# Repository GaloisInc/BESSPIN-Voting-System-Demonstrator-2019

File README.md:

# The BESSPIN Voting System

## Galois and Free & Fair, May-September 2019

# Overview

Galois and Free & Fair are pleased to present the BESSPIN Voting
System (BVS).

The BESSPIN Voting System (BVS) is a demonstration system being funded
by DARPA’s SSITH (System Security Integrated Through Hardware and
Firmware) program. SSITH’s goal is to develop new technologies that
will enable chip designers to safeguard hardware against all known
classes of software-exploitable vulnerabilities, such as memory
errors, information leakage, and code injection.

The BVS demonstration system is intended to showcase the SSITH
program’s results by showing how the innovations of “securitized
hardware” could be applied to a type of critical computing system that
is personally familiar both in use and in importance to millions of
Americans: voting systems. BVS is a combination of voting-system
demonstration software together with prototypes of securitized
hardware being developed by SSITH researchers.

This public repository provides prospective adversarial testers with
complete information, tools, specifications, and source code that was
used to develop the 2019 release of the BVS. The intent is to provide
the most open possible approach to testing, enabling testers to obtain
the full build environment for the BVS, to build it from original
sources, assess its strengths and weaknessess, and plan and develop
possible exploits to compromise the BVS.  

However, not every tester will wish to start with this “Build First”
approach. Others may wish to begin with the “Attacker Quickstart”
information in order to learn and use the tools and reference exploits
provided for testers. Still others may wish to learn about the BVS
with a more manageable “short list” of documentation and information,
rather than exploring the full repository.

# For All Testers

All testers should begin by reading the [Overview of BESSPIN Voting
System](Overview-of-BESSPIN-Voting-System.pdf) document at the top
level of this repository. This document provides essential information
about the current BVS release, the 2019 goals, and limits on testing
including the threat model and win conditions.

# Attacker Quickstart

The top-level directory [Attacker-Quickstart](Attacker-Quickstart)
provides the next level of information after the [Overview of BESSPIN
Voting System](Overview-of-BESSPIN-Voting-System.pdf) document
document, specifically about the facilities provided for exploit
development.

# Documentation on BVS

The top-level directory [BVS-Documents](BVS-Documents) provides the
next level of information after the [Overview of BESSPIN Voting
System](Overview-of-BESSPIN-Voting-System.pdf) document, about the BVS
system’s design and functions.

System design documentation is found in the [docs directory](docs).
In particular, that directory contains:
 - the [BVS 2020 System Specification](docs/BVS 2020 system specification.md)
 - the [BVS 2020 Protocol Specification](docs/protocol.md)
 - the [Smart Ballot Box Specification](docs/sbb.md)
  
# Support for System Build

The remainder of this repository provides the ability to build the BVS
including source code [source](source); specifications [specs](specs);
hardware sketches and schematics [hardware](hardware); documentation
of the build environment [developer-documents](developer-documents);
the top-level [`Makefile`](Makefile) and related files
(`burn_to_flash.sh`, `startup.gdb`); and `.git*` files.

In addition, there is one other source directory for a component that
is not part of the BVS per se, but is part of the test
environment. The [http-log-listener](http-log-listener) directory has
the source code for a software component that runs on a separate
dedicated server that shares the test environment’s LAN with the BVS
Smart Ballot Box systems. The logging software’s purpose is to receive
log data sent by each Smart Ballot Box. Such log consolidation is an
important convenience for the operators of the test environment to be
able to view the activity occuring on the Smart Ballot Box units as
the testers interact with them.

This repository also contains submodules for dependencies that we
manage in other git repositories:
- the RISC-V port of FreeRTOS, which is the lightweight real-time OS
  used for the BVS Smart Ballot Box;
- the top-level toolset for the BESSPIN project;
- the “government furnished equipment” (GFE) repository, which
  contains bitstreams to be uploaded on the FPGAs, and nix shell
  scripts for build set-up.

In order to update those submodules, remember to either clone the
repository using the `--recursive` switch or use the `git submodule
update --init --recursive` command to update the submodules.

The system build process relies on several technologies:
- The core components of the BVS are implemented in the C programming
  language, using the `gcc` and `clang` (LLVM) compilers. C is used
  because the BVS must run on both COTS hardware and SSITH secure
  RISC-V CPUs, and because some SSITH performers are building
  customized versions of the LLVM compiler.
- SSITH CPUs are all based upon the RISC-V Instruction Set
  Architecture (ISA).  Thus, if we must provide any low-level code
  blobs for the BVS in assembly or binary format, they will be written
  in RISC-V assembly code.  Currently there is no such code, nor is it
  necessary at the moment.
- High level specification of BVS is specified using the *Lando*
  specification language, developed under the remit of the BESSPIN
  project at Galois.  Lando is a system specification language geared
  toward describing the shape, structure, behavior, and security of
  high-assurance systems spanning hardware, firmware, and software.
- More detailed and low-level specifications of the BVS are written in
  multiple formal languages. These include *Cryptol*, a DSL for
  specifying and reasoning about bit-level algorithms, particularly
  cryptographic algorithms and protocols, and *ACSL*, the ANSI/ISO C
  Specification Language, for specifying and reasoning about the
  behavior of C programs.

# How to Contribute: Testing the BVS

We welcome all testers to not only perform testing, but also
contribute exploits to this repo. For those attending DEF CON 2019 or
subsequent testing events, the contents of this repo provide ample
resources for detailed preparation, or minimal preparation via the
Attacker Quickstart guide. 

## Live Red Teaming

The following lists the specific steps for how testers’ exploits can
be contributed in a live red teaming framing.

1. Finish reading this README, and the overview document [Overview of
   BESSPIN Voting System](Overview-of-BESSPIN-Voting-System.pdf). Make
   careful note of the threat model and win conditions of the
   system. Only exploits that are in-scope and also meet the win
   conditions with be recognized publicly as as “win” on the system.

2. Choose a target machine.  At DEF CON we have three systems
   available for hacking: 
- A baseline RISC-V microcontroller that has no security
      enhancements. This system can be used to test our your exploits
      on insecure hardware to ensure that they work as expected.
- An open hardware, open source CHERI-RISC-V processor developed
      by SRI and the University of Cambridge.
- A blackbox proprietary secure RISC-V processor.

3. Experiment with an existing exploit in the [Attacker-Quickstart
   directory](Attacker-Quickstart), or write an entirely new
   exploit.  In order to test the exploit, you can either run it in
   software simulation using Verilator, or you can load it onto the
   target machine you have chosen.  We suggest first simulating or
   loading it into a baseline RISC-V processor.

4. Ensure that your exploit provides third-party
   reviewable/demonstrable evidence that the exploit was
   successful. For some exploits, this might be realized via a
   physical mechanism (i.e., you will demonstrate it to organizers
   interactively at DEF CON), and for others, there may be digital
   evidence (i.e., a tampered system log).

5. When you are ready to contribute your exploit, create a personal
   fork of this repository, so that you can provide a merge/pull
   request when you wish to share it with the world and demonstrate
   its capability. We suggest that your exploit be shared in the
   Attacker-Quickstart directory, with a subdirectory with contents
   that follow the conventions of the reference attacks.

6. File an issue in this repo announcing your work to the test
   organizers. In that issue, point to your fork.

7. In the issue body and using the `red-team` labels, please summarize
   your exploit, including indicating which legal weakness you
   exploited (e.g., labels `buffer/memory error` or `information
   leakage`), the behavior of the exploit on insecure hardware, its
   behavior on one of the secure hardware systems, and what evidence
   it provides of your success. Indicate which CPU you targeted with
   the appropriate label, e.g. `baseline`, `SRI/Cambridge`,
   `proprietary`.

8. Talk to an organizer to indicate that you have filed an issue so
   that we can discuss your work face-to-face if desired. Organizers
   will immediately triage your issue and/or merge request.

9. Organizers will review the exploit and will keep you and the public
   up to date about their findings via a public discussion on the
   issue, by using workflow labels `under review`, `success`, `fail`,
   etc.  "Success" in the context of a label means that the exploit
   works on that CPU; "fail" means that it does not. Additional labels
   are used by organizers to label exploits or other code for future
   analysis.

10. Pay attention to the live screens in the testing venue, to see if
    your exploit succeeds or fails.

11. If your exploit is successful (a `CPU-hack` label is applied),
    organizers will summarize your work and success in public
    information on the projection screens at DEF CON or on social
    media.

## Asynchronous Red Teaming

@todo kiniry To be written.

# Credits

This DARPA-funded R&D represents the hard work of the following
employees of Galois and Free & Fair:
 - Alexander Bakst
 - Annie Cherkaev
 - Dan Wallach
 - Dan Zimmmerman
 - Daniel Wagner 
 - Dragan Stosic
 - Dylan Hand
 - Eric Wolridge
 - Flemming Andersen
 - Georgios Dimou
 - Haneef Mubarak
 - Jason Graalum
 - Joe Kiniry
 - Joey Dodds
 - John Sebes
 - Kenny Foner
 - Luke Myers
 - Max Waugaman
 - Michael Podhradsky
 - Nes Cohen
 - Niki Carroll
 - Noah Rich
 - Parker Southwick
 - Reuben Broadfoot
 - Rod Chapman
 - Shpatar Morina
 - Steven Osborn
 - Stuart Pernsteiner

The BMD we are using for DEF CON 2019 is based upon the open source
BMD developed by our friends at [Voting
Works](https://voting.works/). Thanks especially to Ben Adida.

Our fork of Voting Works's BMD for our DEF CON 2019 demonstration is
found on GitHub: https://github.com/GaloisInc/BESSPIN-BMD-2019

This material is based upon work supported by the Defense Advanced Research Project Agency (DARPA) under Contract No. HR0011-18-C-0013.  Any opinions, findings, conclusions or recommendations expressed in this material are those of the author(s) and do not necessarily reflect the views of DARPA.

Distribution Statement "A" (Approved for Public Release, Distribution Unlimited)

# Glossary

For a glossary of voting system terminology, see Free & Fair's
[Election Glossary project at
GitHub](https://github.com/FreeAndFair/ElectionGlossary).  That
glossary is, at the moment, a transliteration of the NIST VVSG
glossary with terms added according to our project needs.  

We also have an informal domain model specified in BON, found in
the [Specifications project at
GitHub](https://github.com/FreeAndFair/Specifications). That domain
model will be updated during BVS 2020 development.

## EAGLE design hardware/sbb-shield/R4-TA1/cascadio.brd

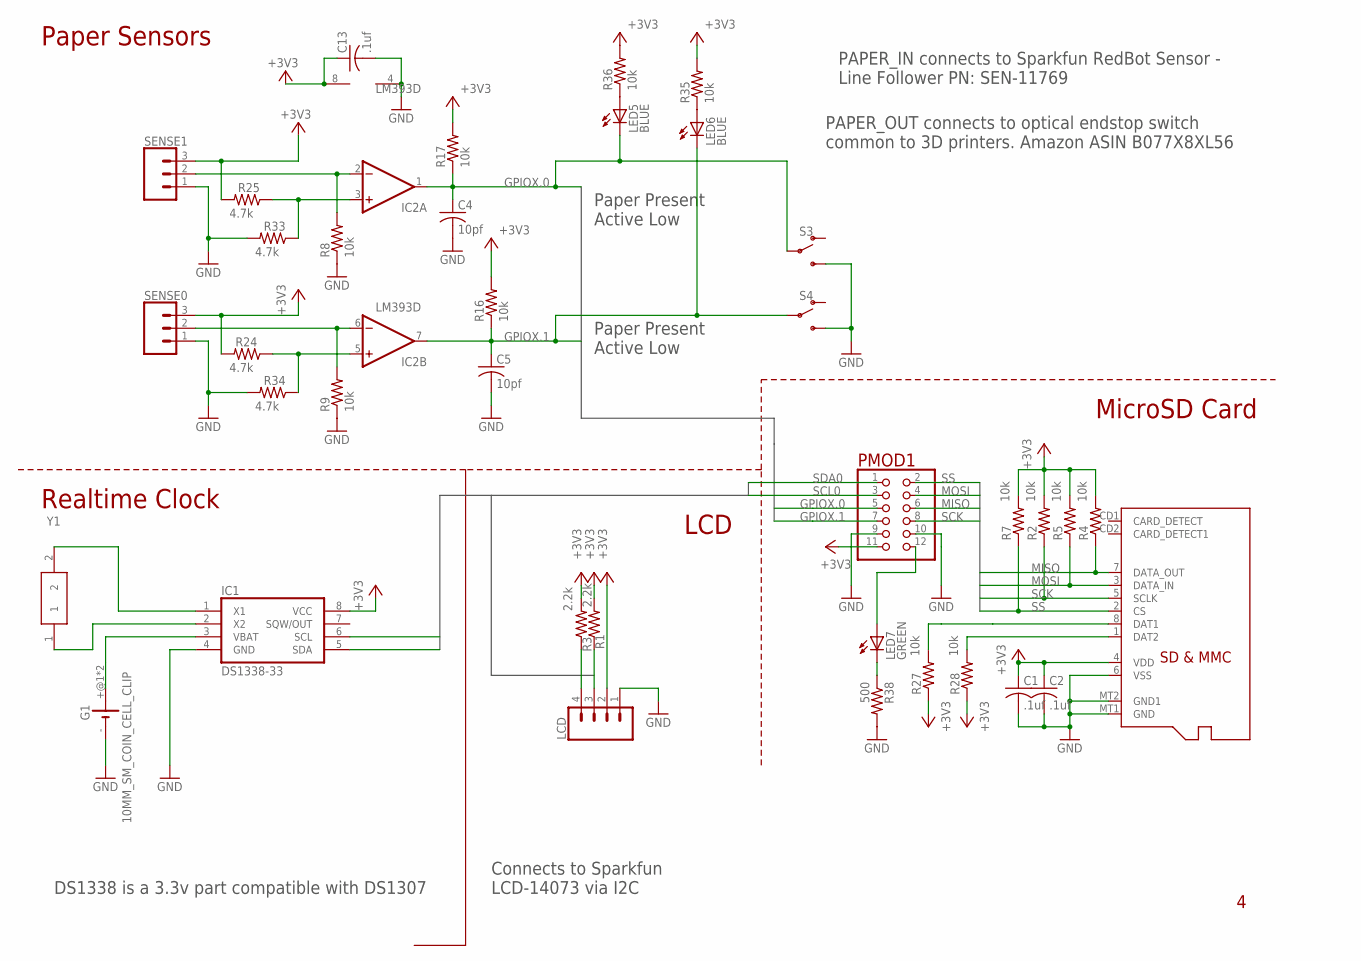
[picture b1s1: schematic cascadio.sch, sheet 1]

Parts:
C1, C2, C13: .1uf; C0603K
C4, C5: 10pf; C0603K
G1: 10MM_SM_COIN_CELL_CLIP
IC1: DS1338-33; SO-8
IC2: LM393D; SO08
LCD: CONN_04POLAR_LOCK; MOLEX-1X4_LOCK
LED5, LED6: BLUE; CHIP-LED0603
LED7: GREEN; CHIP-LED0603
PMOD1: PINHD-2X6; 2X06
R1, R3: 2.2k; R0603
R2, R4, R5, R7, R8, R9, R16, R17, R27, R28, R35, R36: 10k; R0603
R24, R25, R33, R34: 4.7k; R0603
R38: 500; R0603
S3, S4: SPDT_TOGGLE_BUTTONMICRO; BTN-PUSH-PUSH-PS-2214-L
SENSE0: SENSE0; MOLEX-1X3_LOCK
SENSE1: CONN_03POLAR_LOCK; MOLEX-1X3_LOCK
U1: MICROSD
Y1: 32.768khz; ABS07AIG32768KHZ71T

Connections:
+3V3: C1.1, C2.1, C13.1, IC1.8 (VCC), IC2.8 (V+), LCD.2, PMOD1.11, R1.2, R2.2, R3.2, R4.2, R5.2, R7.2, R16.2, R17.2, R24.2, R25.2, R27.1, R28.1, R35.2, R36.2, SENSE0.3, SENSE1.3, U1.4 (VDD); also elsewhere on the board
GND: C1.2, C2.2, C4.2, C5.2, C13.2, G1.-, IC1.4 (GND), IC2.4 (V-), LCD.1, PMOD1.9, PMOD1.10, R8.1, R9.1, R33.2, R34.2, R38.2, S3.NO0 (S), S3.NO1 (S), S4.NO0 (S), S4.NO1 (S), SENSE0.1, SENSE1.1, U1.6 (VSS), U1.MT1 (GND), U1.MT2 (GND1); also elsewhere on the board
GPIOX.0: C4.1, IC2.1 (OUT), LED5.C, PMOD1.5, R17.1, S3.C0, S3.C1; also elsewhere on the board
GPIOX.1: C5.1, IC2.7 (OUT), LED6.C, PMOD1.7, R16.1, S4.C0, S4.C1; also elsewhere on the board
MISO: PMOD1.6, R4.1, U1.7 (DATA_OUT); also elsewhere on the board
MOSI: PMOD1.4, R5.1, U1.3 (DATA_IN); also elsewhere on the board
unnamed: IC2.5 (+IN), R24.1, R34.1
unnamed: IC2.3 (+IN), R25.1, R33.1
unnamed: IC1.1 (X1), Y1.2
unnamed: R27.2, U1.8 (DAT1)
unnamed: R28.2, U1.1 (DAT2)
unnamed: IC1.2 (X2), Y1.1
unnamed: G1.+@1 (+), G1.+@2 (+), IC1.3 (VBAT)
unnamed: IC2.2 (-IN), R8.2, SENSE1.2
unnamed: IC2.6 (-IN), R9.2, SENSE0.2
unnamed: LED6.A, R35.1
unnamed: LED5.A, R36.1
unnamed: LED7.C, R38.1
unnamed: LED7.A, PMOD1.12
SCK: PMOD1.8, R2.1, U1.5 (SCLK); also elsewhere on the board
SCL0: IC1.6 (SCL), LCD.4, PMOD1.3, R3.1; also elsewhere on the board
SDA0: IC1.5 (SDA), LCD.3, PMOD1.1, R1.1; also elsewhere on the board
SS: PMOD1.2, R7.1, U1.2 (CS); also elsewhere on the board

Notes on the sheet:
LCD
MicroSD Card
Paper Sensors
Realtime Clock
Connects to Sparkfun LCD-14073 via I2C
DS1338 is a 3.3v part compatible with DS1307
PAPER_IN connects to Sparkfun RedBot Sensor - Line Follower PN: SEN-11769
PAPER_OUT connects to optical endstop switch common to 3D printers. Amazon ASIN B077X8XL56
Paper Present Active Low

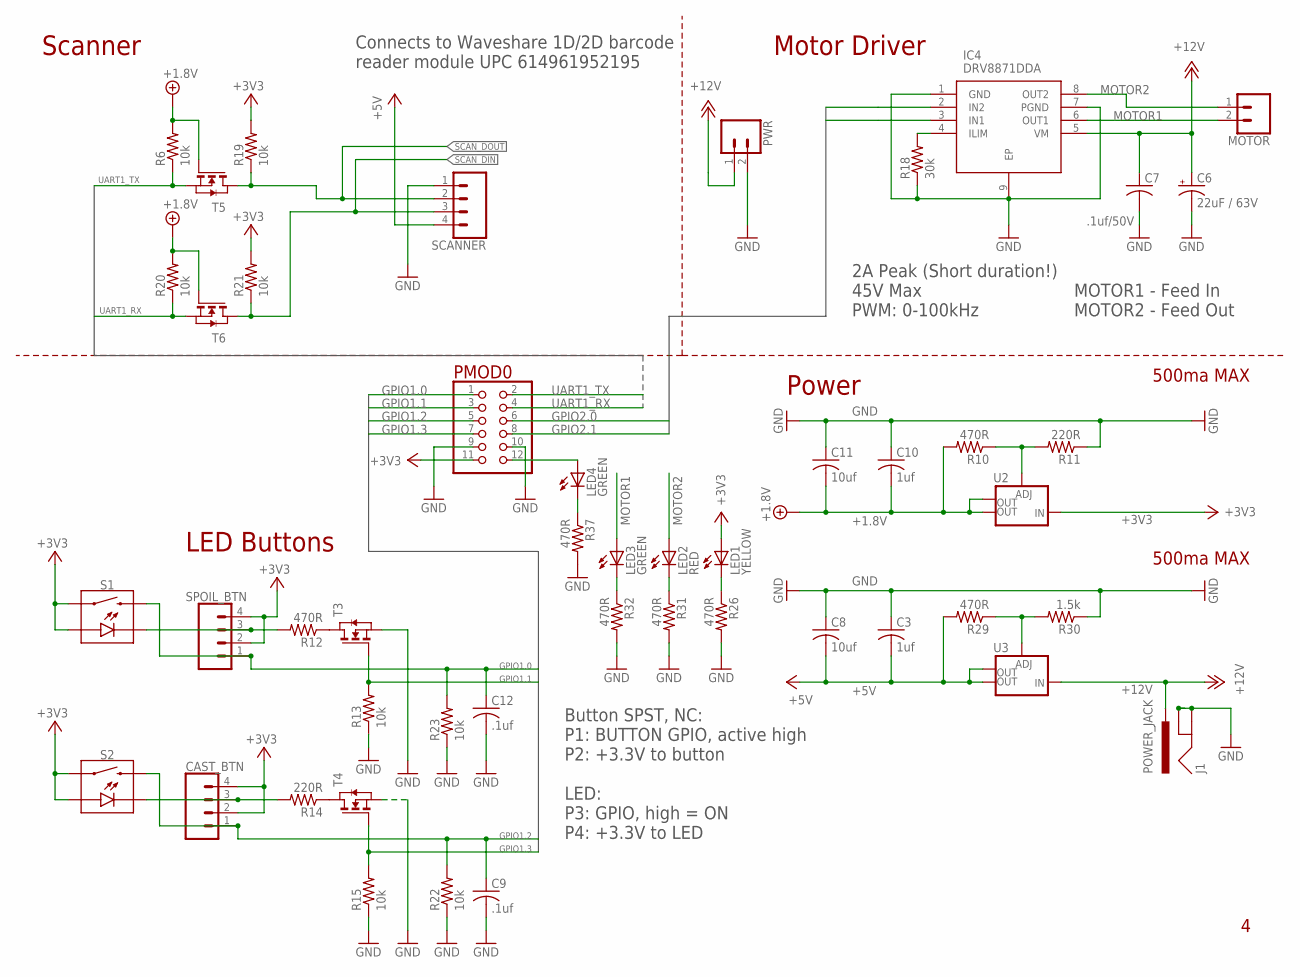
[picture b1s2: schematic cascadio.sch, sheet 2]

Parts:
C3, C10: 1uf; C0603K
C6: 22uF / 63V; PANASONIC_D
C7: .1uf/50V; C0805K
C8, C11: 10uf; C1206K
C9, C12: .1uf; C0603K
CAST_BTN: CONN_04POLAR_LOCK; MOLEX-1X4_LOCK
IC4: DRV8871DDA; SOIC127P600X170-9N
J1: POWER_JACK; POWER_JACK_PTH
LED1: YELLOW; CHIP-LED0603
LED2: RED; CHIP-LED0603
LED3, LED4: GREEN; CHIP-LED0603
MOTOR: CONN_02POLAR_LOCK; MOLEX-1X2_LOCK
PMOD0: PINHD-2X6; 2X06
PWR: CONN_02POLAR_LOCK; MOLEX-1X2_LOCK
R6, R13, R15, R19, R20, R21, R22, R23: 10k; R0603
R10, R12, R26, R29, R31, R32, R37: 470R; R0603
R11, R14: 220R; R0603
R18: 30k; R0603
R30: 1.5k; R0603
S1, S2: MOMENTARY-SWITCH-SPST-LED-PTH-12MM; TACTILE_SWITCH_LED_PTH_12MM
SCANNER: CONN_04POLAR_LOCK; MOLEX-1X4_LOCK
SPOIL_BTN: CONN_04POLAR_LOCK; MOLEX-1X4_LOCK
T3, T4, T5, T6: PMV65UNEAR; SOT-23
U2, U3: V_REG_LM1117SOT223; SOT223

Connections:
+1.8V: C10.2, C11.2, R6.2, R10.2, R20.2, T5.3 (G), T6.3 (G), U2.2 (OUT), U2.4 (OUT)
+3V3: CAST_BTN.2, CAST_BTN.4, LED1.A, PMOD0.11, R19.2, R21.2, S1.4 (1), S1.A, S2.4 (1), S2.A, SPOIL_BTN.2, SPOIL_BTN.4, U2.3 (IN); also elsewhere on the board
+5V: C3.2, C8.2, R29.2, SCANNER.4, U3.2 (OUT), U3.4 (OUT)
+12V: C6.+, C7.1, IC4.5 (VM), J1.PWR, PWR.1, U3.3 (IN)
GND: C3.1, C6.-, C7.2, C8.1, C9.2, C10.1, C11.1, C12.2, IC4.1 (GND), IC4.7 (PGND), IC4.9 (EP), J1.GND, J1.GNDBREAK, PMOD0.9, PMOD0.10, PWR.2, R11.1, R13.1, R15.1, R18.1, R22.1, R23.1, R26.2, R30.1, R31.2, R32.2, R37.2, SCANNER.1, T3.2 (S), T4.2 (S); also elsewhere on the board
GPIO1.0: C12.1, PMOD0.1, R23.2, S1.2, SPOIL_BTN.1; also elsewhere on the board
GPIO1.1: PMOD0.3, R13.2, T3.3 (G); also elsewhere on the board
GPIO1.2: C9.1, CAST_BTN.1, PMOD0.5, R22.2, S2.2; also elsewhere on the board
GPIO1.3: PMOD0.7, R15.2, T4.3 (G); also elsewhere on the board
GPIO2.0: IC4.2 (IN2), PMOD0.6; also elsewhere on the board
GPIO2.1: IC4.3 (IN1), PMOD0.8; also elsewhere on the board
MOTOR1: IC4.6 (OUT1), LED3.A, MOTOR.2
MOTOR2: IC4.8 (OUT2), LED2.A, MOTOR.1
unnamed: LED1.C, R26.1
unnamed: R12.1, T3.1 (D)
unnamed: R29.1, R30.2, U3.1 (ADJ)
unnamed: R10.1, R11.2, U2.1 (ADJ)
unnamed: R12.2, S1.C, SPOIL_BTN.3
unnamed: LED2.C, R31.1
unnamed: LED3.C, R32.1
unnamed: LED4.A, PMOD0.12
unnamed: LED4.C, R37.1
unnamed: R14.1, T4.1 (D)
unnamed: IC4.4 (ILIM), R18.2
unnamed: CAST_BTN.3, R14.2, S2.C
SCAN_DIN: R21.1, SCANNER.3, T6.1 (D); also elsewhere on the board
SCAN_DOUT: R19.1, SCANNER.2, T5.1 (D); also elsewhere on the board
UART1_RX: PMOD0.4, R20.1, T6.2 (S)
UART1_TX: PMOD0.2, R6.1, T5.2 (S)

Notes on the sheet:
Motor Driver
Scanner
LED Buttons
Power
Connects to Waveshare 1D/2D barcode reader module UPC 614961952195
500ma MAX
Button SPST, NC: P1: BUTTON GPIO, active high P2: +3.3V to button LED: P3: GPIO, high = ON P4: +3.3V to LED
2A Peak (Short duration!) 45V Max PWM: 0-100kHz
MOTOR1 - Feed In MOTOR2 - Feed Out

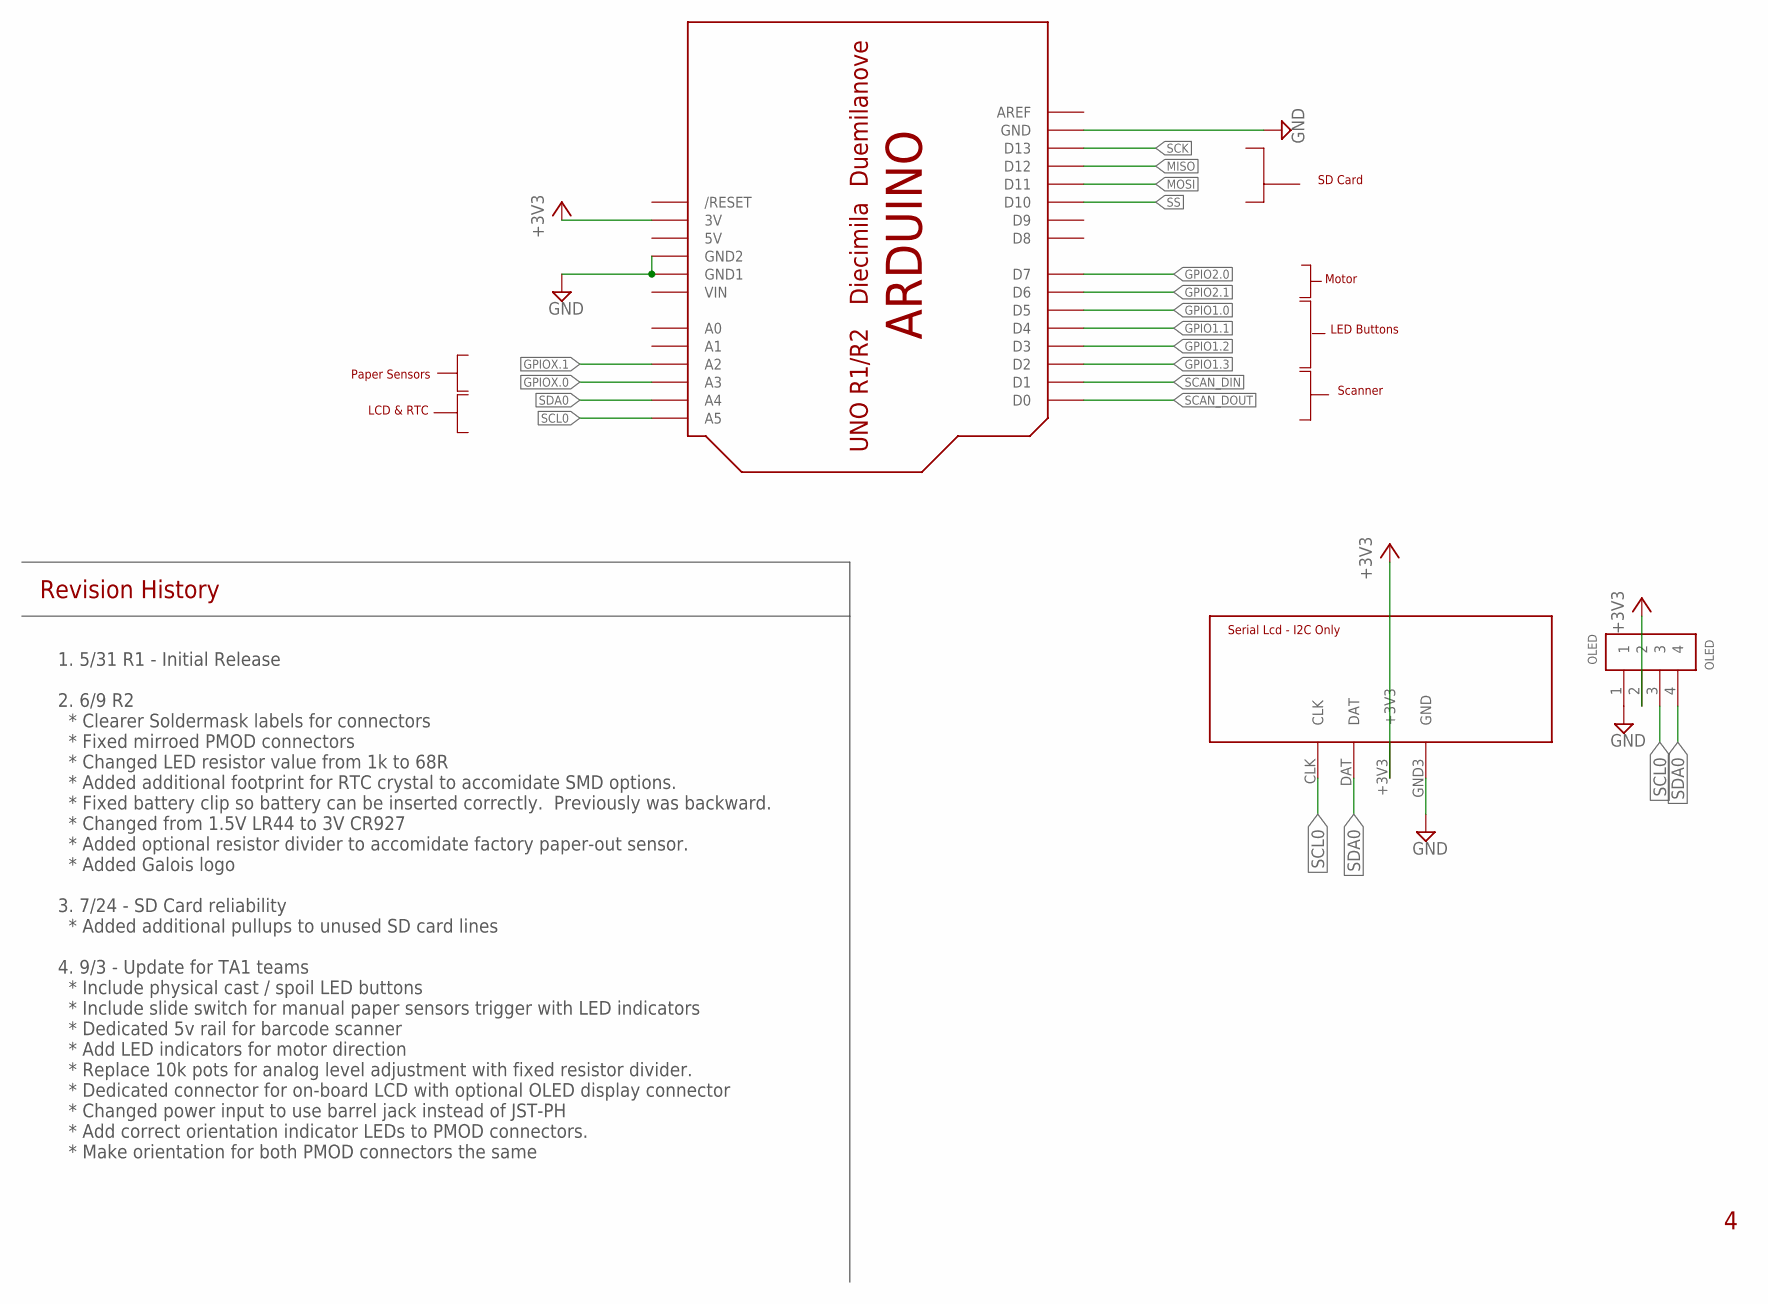
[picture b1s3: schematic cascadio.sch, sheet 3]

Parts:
OLED: OLED; 1X04-CLEANBIG
U$1: SERLCD_I2C; SERLCD
U$2: ARDUINO-NOHOLE

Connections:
5V: U$2.5V
+3V3: OLED.2, U$1.+3V3, U$2.3V; also elsewhere on the board
GND: OLED.1, U$1.GND3 (GND), U$2.GND, U$2.GND1, U$2.GND2; also elsewhere on the board
GPIO1.0: U$2.D5; also elsewhere on the board
GPIO1.1: U$2.D4; also elsewhere on the board
GPIO1.2: U$2.D3; also elsewhere on the board
GPIO1.3: U$2.D2; also elsewhere on the board
GPIO2.0: U$2.D7; also elsewhere on the board
GPIO2.1: U$2.D6; also elsewhere on the board
GPIOX.0: U$2.A3; also elsewhere on the board
GPIOX.1: U$2.A2; also elsewhere on the board
MISO: U$2.D12; also elsewhere on the board
MOSI: U$2.D11; also elsewhere on the board
SCAN_DIN: U$2.D1; also elsewhere on the board
SCAN_DOUT: U$2.D0; also elsewhere on the board
SCK: U$2.D13; also elsewhere on the board
SCL0: OLED.3, U$1.CLK, U$2.A5; also elsewhere on the board
SDA0: OLED.4, U$1.DAT, U$2.A4; also elsewhere on the board
SS: U$2.D10; also elsewhere on the board
VIN: U$2.VIN

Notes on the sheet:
SD Card
Scanner
LCD & RTC
LED Buttons
Motor
Paper Sensors
Revision History
1. 5/31 R1 - Initial Release 2. 6/9 R2 * Clearer Soldermask labels for connectors * Fixed mirroed PMOD connectors * Changed LED resistor value from 1k to 68R * Added additional footprint for RTC crystal to accomidate SMD options. * Fixed battery clip so battery can be inserted correctly. Previously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

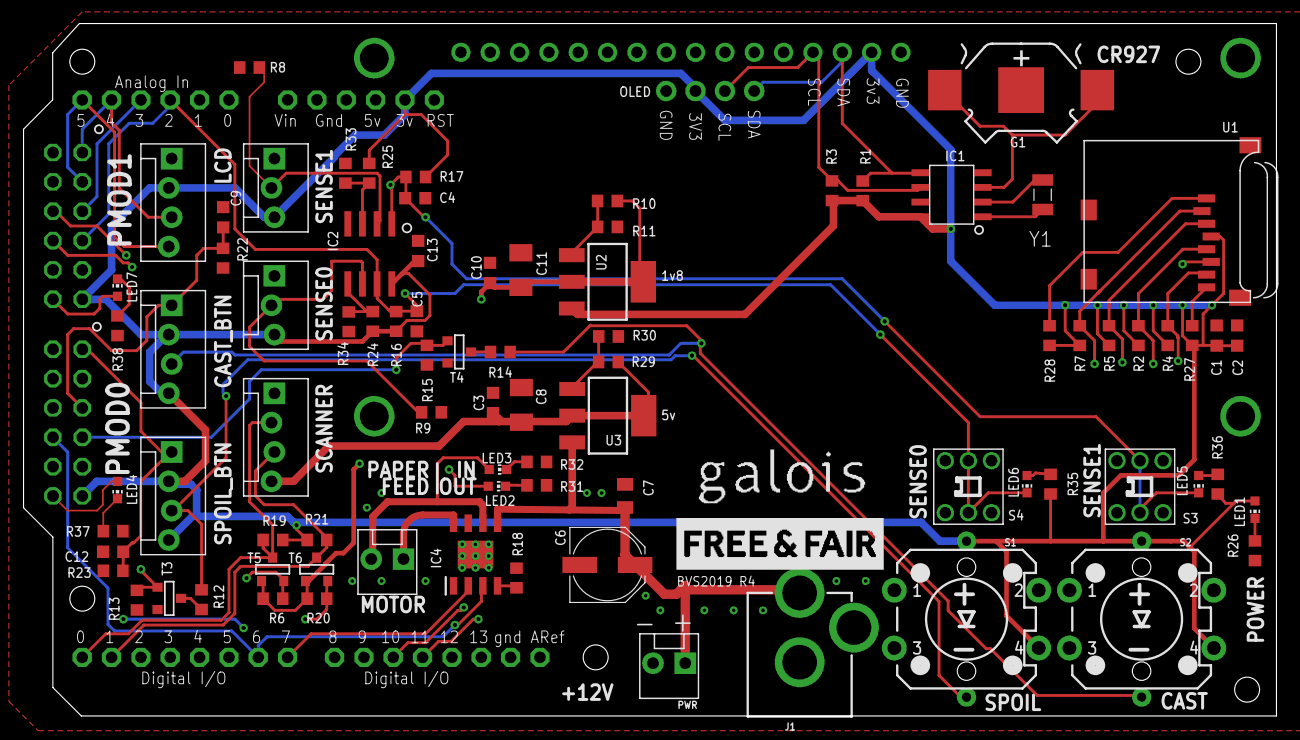
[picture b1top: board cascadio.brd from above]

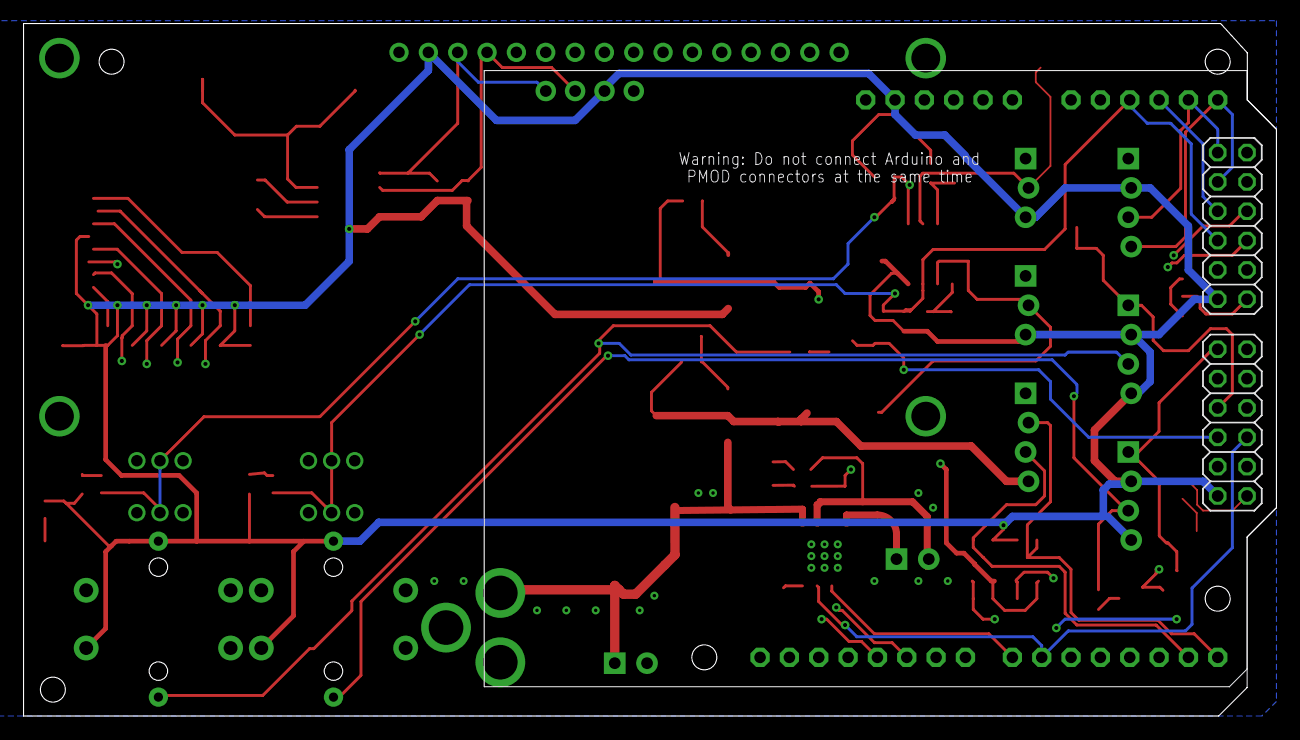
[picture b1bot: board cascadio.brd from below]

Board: 4 copper layers, 108.5 x 59.9 mm, 88 parts (2 on the bottom side), 50 nets.

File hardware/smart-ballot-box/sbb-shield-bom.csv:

"Qty";"Value";"Device";"Package";"Parts";"Description";"DESCRIPTION";"HEIGHT";"MANUFACTURER_NAME";"MANUFACTURER_PART_NUMBER";"MF";"MOUSER_PART_NUMBER";"MOUSER_PRICE-STOCK";"MPN";"OC_FARNELL";"OC_NEWARK";"PROD_ID";"SF_ID";"SPICEPREFIX";
"1";"";"CONN_022.54MM_SCREWTERM";"1X02_2.54_SCREWTERM";"J1";"Multi connection point. Often used as Generic Header-pin footprint for 0.1 inch spaced/style header connections";"";"";"";"";"";"";"";"";"";"";"";"";"";
"1";"";"CONN_02POLAR_LOCK";"MOLEX-1X2_LOCK";"MOTOR";"Multi connection point. Often used as Generic Header-pin footprint for 0.1 inch spaced/style header connections";"";"";"";"";"";"";"";"";"";"";"";"PRT-09918";"";
"2";"";"CONN_03POLAR_LOCK";"MOLEX-1X3_LOCK";"PAPER_IN, PAPER_OUT";"Multi connection point. Often used as Generic Header-pin footprint for 0.1 inch spaced/style header connections";"";"";"";"";"";"";"";"";"";"";"CONN-08625";"PRT-08096";"";
"4";"";"CONN_04POLAR_LOCK";"MOLEX-1X4_LOCK";"CAST_BTN, LCD, SCANNER, SPOIL_BTN";"Multi connection point. Often used as Generic Header-pin footprint for 0.1 inch spaced/style header connections";"";"";"";"";"";"";"";"";"";"";"CONN-08186";"PRT-08231";"";
"2";"";"PINHD-2X6";"2X06";"PMOD0, PMOD1";"PIN HEADER";"";"";"";"";"";"";"";"";"";"";"";"";"";
"1";"";"V_REG_LM1117SOT223";"SOT223";"U2";"Voltage Regulator LM1117";"";"";"";"";"";"";"";"";"";"";"VREG-08170";"";"";
"2";".1uf";"C-USC0603K";"C0603K";"C1, C13";"CAPACITOR, American symbol";"";"";"";"";"";"";"";"";"";"";"";"";"";
"2";".1uf";"C-USC0603K";"C0603K";"C9, C12";"CAPACITOR, American symbol";"";"";"";"";"";"";"";"";"";"";"";"";"C";
"1";".1uf/50V";"C-USC0805K";"C0805K";"C7";"CAPACITOR, American symbol";"";"";"";"";"";"";"";"";"";"";"";"";"";
"1";"100R";"R-US_R0603";"R0603";"R9";"RESISTOR, American symbol";"";"";"";"";"";"";"";"";"";"";"";"";"";
"1";"10MM_SM_COIN_CELL_CLIP";"10MM_SM_COIN_CELL_CLIP";"10MM_SM_COIN_CELL_CLIP";"G1";"Battery cell clip for CR927";"";"";"";"";"";"";"";"";"";"";"";"";"";
"14";"10k";"R-US_R0603";"R0603";"R2, R4, R5, R6, R7, R13, R15, R16, R17, R19, R20, R21, R22, R23";"RESISTOR, American symbol";"";"";"";"";"";"";"";"";"";"";"";"";"";
"2";"10k";"TRIMPOTTC33X";"TC33X";"TM1, TM2";"SMT trimmer potentiometer part number TC33X";"";"";"";"";"";"";"";"";"";"";"";"";"";
"2";"10pf";"C-USC0603K";"C0603K";"C4, C5";"CAPACITOR, American symbol";"";"";"";"";"";"";"";"";"";"";"";"";"";
"1";"10uf";"C-USC1206K";"C1206K";"C11";"CAPACITOR, American symbol";"";"";"";"";"";"";"";"";"";"";"";"";"";
"1";"1uf";"C-USC0603K";"C0603K";"C10";"CAPACITOR, American symbol";"";"";"";"";"";"";"";"";"";"";"";"";"C";
"2";"2.2k";"R-US_R0603";"R0603";"R1, R3";"RESISTOR, American symbol";"";"";"";"";"";"";"";"";"";"";"";"";"";
"1";"220";"R-US_R0603";"R0603";"R11";"RESISTOR, American symbol";"";"";"";"";"";"";"";"";"";"";"";"";"";
"1";"22uF / 63V";"CPOL-USD";"PANASONIC_D";"C6";"POLARIZED CAPACITOR, American symbol";"";"";"";"";"";"";"";"";"";"";"";"";"";
"1";"30k";"R-US_R0603";"R0603";"R18";"RESISTOR, American symbol";"";"";"";"";"";"";"";"";"";"";"";"";"";
"1";"32.768khz";"ABS07W-32.768KHZ-D-1-T";"ABS07AIG32768KHZ71T";"Y1";"Abracon 32.768kHz Crystal 2-SMD, No Lead 3.2 x1.5 x 0.9mm";"Abracon 32.768kHz Crystal 2-SMD, No Lead 3.2 x1.5 x 0.9mm";"0mm";"ABRACON";"ABS07W-32.768kHz-D-1-T";"";"815-ABS07W32.768KD1T";"https://www.mouser.com/Search/Refine.aspx?Keyword=815-ABS07W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";"";"";"";"";"";"";
"1";"32.768khz";"CRYSTALTC26H";"TC26H";"Q1";"CRYSTAL";"";"";"";"";"";"";"";"";"unknown";"unknown";"";"";"";
"2";"33k";"R-US_R0603";"R0603";"R24, R25";"RESISTOR, American symbol";"";"";"";"";"";"";"";"";"";"";"";"";"";
"1";"500";"R-US_R0603";"R0603";"R10";"RESISTOR, American symbol";"";"";"";"";"";"";"";"";"";"";"";"";"";
"3";"68R";"R-US_R0603";"R0603";"R8, R12, R14";"RESISTOR, American symbol";"";"";"";"";"";"";"";"";"";"";"";"";"";
"1";"ARDUINO-NOHOLE";"ARDUINO-NOHOLE";"ARDUINO-NOHOLE";"U$2";"Arduino Diecimila/Duemilanove";"";"";"";"";"";"";"";"";"";"";"";"";"";
"1";"DRV8871DDA";"DRV8871DDA";"SOIC127P600X170-9N";"IC4";"Motor / Motion / Ignition Controllers & Drivers 3.6A Brushed DC Motor Driver with Integrated Current Sensing (PWM Ctrl) 8-SO PowerPAD -40 to 125";"Motor / Motion / Ignition Controllers & Drivers 3.6A Brushed DC Motor Driver with Integrated Current Sensing (PWM Ctrl) 8-SO PowerPAD -40 to 125";"1.7mm";"Texas Instruments";"DRV8871DDA";"";"595-DRV8871DDA";"https://www.mouser.com/Search/Refine.aspx?Keyword=595-DRV8871DDA";"";"";"";"";"";"";
"1";"DS1338-33";"IC_RTC_DS1307";"SO-8";"IC1";"";"";"";"";"";"";"";"";"";"";"";"";"";"";
"1";"LM393D";"LM393D";"SO08";"IC2";"COMPARATOR";"";"";"";"";"";"";"";"";"";"";"";"";"";
"1";"MICROSD";"MICROSD";"MICROSD";"U1";"Micro-SD / Transflash card holder with SPI pinout";"";"";"";"";"";"";"";"";"";"";"";"";"";
"4";"PMV65UNEAR";"NMOSSOT23";"SOT-23";"T3, T4, T5, T6";"MOS FET";"";"";"";"";"";"";"";"";"unknown";"unknown";"";"";"";

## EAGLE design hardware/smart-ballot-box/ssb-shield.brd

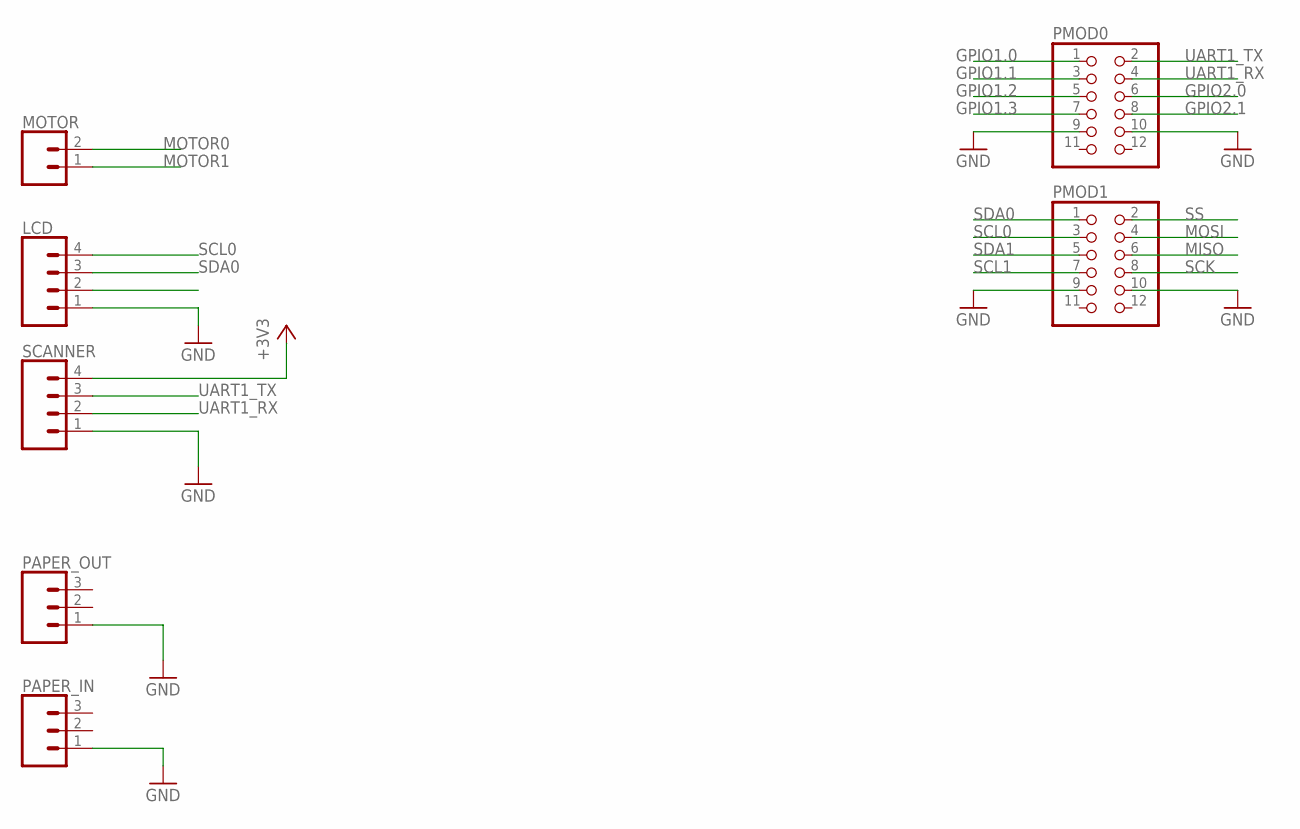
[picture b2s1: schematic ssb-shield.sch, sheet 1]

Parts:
LCD: CONN_04POLAR_LOCK; MOLEX-1X4_LOCK
MOTOR: CONN_02POLAR_LOCK; MOLEX-1X2_LOCK
PAPER_IN: CONN_03POLAR_LOCK; MOLEX-1X3_LOCK
PAPER_OUT: CONN_03POLAR_LOCK; MOLEX-1X3_LOCK
PMOD0, PMOD1: PINHD-2X6; 2X06
SCANNER: CONN_04POLAR_LOCK; MOLEX-1X4_LOCK

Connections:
+3V3: SCANNER.4; also elsewhere on the board
GND: LCD.1, PAPER_IN.1, PAPER_OUT.1, PMOD0.9, PMOD0.10, PMOD1.9, PMOD1.10, SCANNER.1; also elsewhere on the board
GPIO1.0: PMOD0.1
GPIO1.1: PMOD0.3
GPIO1.2: PMOD0.5
GPIO1.3: PMOD0.7
GPIO2.0: PMOD0.6
GPIO2.1: PMOD0.8
MISO: PMOD1.6
MOSI: PMOD1.4
MOTOR0: MOTOR.2
MOTOR1: MOTOR.1
SCK: PMOD1.8
SCL0: LCD.4, PMOD1.3
SCL1: PMOD1.7
SDA0: LCD.3, PMOD1.1
SDA1: PMOD1.5
SS: PMOD1.2
UART1_RX: PMOD0.4, SCANNER.2
UART1_TX: PMOD0.2, SCANNER.3

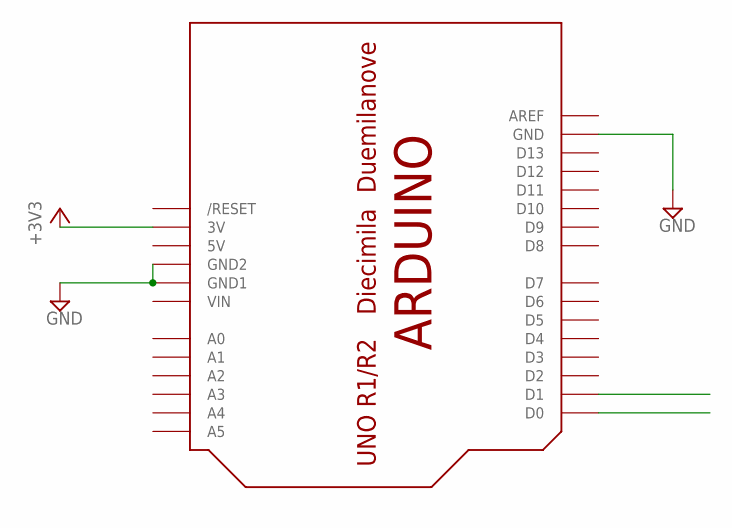
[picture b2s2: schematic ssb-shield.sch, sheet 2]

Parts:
U$2: ARDUINO-NOHOLE

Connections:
5V: U$2.5V
+3V3: U$2.3V; also elsewhere on the board
GND: U$2.GND, U$2.GND1, U$2.GND2; also elsewhere on the board
VIN: U$2.VIN

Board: 2 copper layers, 8 parts (0 on the bottom side), 6 nets, no tracks yet.

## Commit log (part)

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2019-08-06 included base64.acsl
2019-08-06 Restored version of Base64.cry from pre-rebase.
2019-08-07 initial commit with skeleton examples
2019-08-07 AES example, added missing assembly
2019-08-08 second example exploit
2019-08-09 Enable clang compilation
2019-08-09 Add conference materials
2019-08-09 Reorganizes exploit subdirectories and closes #112.
    Former-commit-id: 6cf5f58bc76f98e3074801c880ee695de37cd9b6
2019-08-09 No GPIO calls in simulation.
    Former-commit-id: c7c49df263a8ac35336c2829ac40df1399117ec3
2019-08-09 Updated the buffer handling code to have a vulnerability.
    Former-commit-id: ea1974636bf3468739290b07a74223013be73c19
2019-08-09 Enable input task
    Former-commit-id: 557a97a63885fb09f0c16b4098675e76c3bdfd80
2019-08-09 Cleaned up some output, fixed call to base64 decode.
    Former-commit-id: e57191d7fdf7209e1df6f50802b86f80bf72d194
2019-08-09 Fixed echoing and probably fixed Base64 decoding of malware.
    Former-commit-id: c8fb469d1748f82b6822e538cfa225beb8448f1e
2019-08-09 Removed the msleep from the UART reads.
    Former-commit-id: 99ce6c46fee8b7f603336056f97da9568a9873cc
2019-08-09 FAQ Approved by DARPA
    Former-commit-id: 01f1fb2bb37d7cf8bb64b2d9cfc5d64dd2a084a2
2019-08-09 Bump FreeRTOS
    Former-commit-id: 4521871f146d06848ca010931755424c036e679a
2019-08-10 Fixed all links in documentation.
    Former-commit-id: f7f7ed1126a804b72000df74f229afe18e925ec7
2019-08-16 Strengthen precondition of Prepare_Transmit_Buffer.
    Former-commit-id: 348a0733f25b37ba03a7498bd267389bc93672bb
2019-08-16 Refactor Prepare_Transmit_Buffer more to simplify proof further.
    Former-commit-id: f9a728802d7ce9726cf1554662e744b23e5123ed
2019-08-16 Use new predicates supporting a length-limited log file name.
    Former-commit-id: ae8c37608e6b3020a259bd3bb126788f5aa27a51
2019-08-16 Add const qualifier to IN parameter src for array copy functions.
    Former-commit-id: 2825df8d274a9b8b955f3c9e1bc6d1d6b7c81085
2019-08-22 Decryption spec complete, sans decimal representation
    Former-commit-id: 158a5ae4d73ef11de20bae4f1107a4d2fbc767f0
2019-08-22 Suppress defaulting warnings by adding annotations
    Former-commit-id: a86582e0474dfec5dd60fc6b0b0f384630dae6e7
2019-08-22 Remove sequence number from ballot type
    Former-commit-id: 93609826ab71599b197163c36851240e26919d0f
2019-08-22 Update to Cryptol 2.7.0, fix errors
    Former-commit-id: 74c46b14bc8e8469d1d4355f3a732bbc36ad61c7
2019-08-22 Use zero IV for encryption/decryption since we'll never repeat a ballot
    Former-commit-id: af34116433a6473e19e77c11648abd625d5a04df
2019-08-22 Add further documentation about the properties defined for the ballot format
    Former-commit-id: d596bd6fc41be5e1cc754890c43080fdc053fd62
2019-08-24 fixed recursive sextets - replacing predefined types
    Former-commit-id: c3d547c80047fc0018a08cc3bf7a2aeb8c3eb1bd
2019-08-24 redesign - preparing spec for the base64.acsl
    Former-commit-id: 68aed1fd0e09b950def858eabfa06203f58e373c
2019-08-24 guard correction in padWith function
    Former-commit-id: 1d9776e432a89298378e701ced1f6387aaeef39e
2019-08-24 added padWith and rightPadWith func def and test lemmas
    Former-commit-id: 80f487a1348265d7649d123f8a15e1c2a2e6b257
2019-08-24 added ASSURANCE.md
    Former-commit-id: 43cda6d8dafa65fa2d69d06e2aa0af3a75605719
2019-08-25 SBB axiomatics
    Former-commit-id: 963c2787dedd19354ccc7380c8a446376b56c879
2019-08-29 Add ASM diagrams.
    Former-commit-id: 9869cbfb487f0545bb6b06d3ffa6f170461a66fd
2019-08-30 Set address sanitizer for hosttests
    Former-commit-id: 8df3381b2eabde9da3a3ac95024983e2b3ed0a60
2019-08-30 Reduce number of makefiles for freertos.
    Former-commit-id: b0d1b52d68f6e59c455bf4ec4ac5e16ab3a5ce33
2019-08-30 Fix hosttest targets.
    Former-commit-id: 01b181557ce5ecae8e1a57bebc35d49a3d543413
2019-08-30 Split OSD code from log_net.c
    Former-commit-id: 5f3f45d3bc75df4dc659fbf2116cc442d7bfb0c6
2019-08-30 Makefile.freertos should append to CFLAGS, not redefine it.
    Former-commit-id: 4587aeb2a9891372ddafa5f0e61e0070cfb30ac1
2019-08-30 Fix target inconsistency and if/endif closing comment.
    Former-commit-id: 69c8f911011896a5bbc75ce77d346d65db47886f
2019-08-30 set verification OS to posix.
    Former-commit-id: 5805616647ee93b4d938d609cf53fa1192a7d4d2
2019-08-30 Some fs related fixes for tests
    Former-commit-id: c0cdf399503809c8eca1a5340ac8de39bfb942a4
2019-09-04 Fixed spacing in debug_io.c
    Former-commit-id: 34a5612de43a65ee09d4458fd2f5f09c011b1f56
2019-09-09 Initial posix simulator implementation.
    Former-commit-id: 4e1ed437801ea7bce59c89366d7d6da3b5d61f9a
2019-09-16 Factor out OSD/OSI log_fs code.
    Former-commit-id: 8b4090740bd7b442c266c64e79c9b46657f0a44b
2019-09-18 Correct definition of valid_log_file_name predicate
    Former-commit-id: 49ed1747030e1f111ba2bd35f03a060b24883b5a
2019-09-18 Use named constants instead of literals in definition of Good_String predicate.
    Former-commit-id: f9d6de20f8c5819e03230521007bfcf2f053404f
2019-09-19 Use Frama-C 19's -eva-precision option set to 11 (maximum depth).
    Former-commit-id: b1cc49d4a9ab2f66953ee80b996f9ca0d5ea6ed8
2019-09-25 preparation for Thursday and Friday's working sessions
    Former-commit-id: c175223ce935d5cf6604ce8c681221b747b82d13
2019-09-25 Updated development plan for BVS 2020's SBB.
    Former-commit-id: 6f1f4e97d91c799fb4560af711a65e846163572d
2019-09-25 First draft of top-level system requirements.
    Former-commit-id: 8922672b26c3f3a8a990bd0aad8c6581c1f7a0f0
2019-09-25 Made protocol state more clearly called out.
    Former-commit-id: 5f60f04fc329bc315eef881cc029e32fd8adfdae
2019-09-25 Continued work on !156, particular wrt manifests and glossary.
    Former-commit-id: 48b45bbfdd24e6710c1bb089bff1e7d64a6b2985
2019-09-26 Fix unused param.
    Former-commit-id: c2658b3807ccc4fa25cdc0eaf1aea9a350965de7
2019-09-27 I have revised all Lando syntax to reflect its current definition.
    Former-commit-id: 6efc11ddd94efb3fc9d44283b2464ba5ecf90a29
2019-10-04 Docker for good
    Former-commit-id: 8e3356130c20139379fac8bdb2a18ca79d9c50c0
2019-10-08 fixed name and markdown link
    Former-commit-id: ff24185ae4bd31cebd32bd76a73a60ba187851a7
2019-10-08 added availability
    Former-commit-id: 7cee044bfa8e8e8dfc2ec8bd0e69a8040987fa59
2019-10-08 Update Evidence_Server.md
    Former-commit-id: db74494ae8cb5cfa0adcf0567a25d4d24f3ef356
2019-10-08 Initial work on evidence server readme.
    Former-commit-id: fa4f57f1f4eb2723abbcd409b18235901114d271
2019-10-08 Address @hmubarak's comments
    Former-commit-id: bb05bb5d5f2fd028c7d378edf507ed6a20892179
2019-10-08 Assign todos.
    Former-commit-id: 11e67959cfbba4d444e8acf42952422ff60be9eb
2019-10-08 fixed typos
    Former-commit-id: 5cb42d35e11ca8e86500410734a072140841c3e7
2019-10-08 fixed typos
    Former-commit-id: d0ddd4ebe6a8df628ed7b8038952e7f85df66446
2019-10-10 docs/vps: more precise but natural @todo syntax and also TIL apparently I can't spell my own name
    Former-commit-id: ab9eb941fc17146327489a400a05eab0532c2e2a
2019-10-10 Apply suggestion to specs/lando/specs/lando/vps/plan.lando
    Former-commit-id: 22ce56538354d3bd110f999eff49cb2cbc0ff6a6
2019-10-10 make VPS Plando reflect #198
    Former-commit-id: f0fb33b046fe43296d656cc1ead9a259b103f93f
2019-10-11 First draft of Tabulation_Device.md
    Former-commit-id: 60d459e5dd542999d935cb3e2c9bda46b8a37da7
2019-10-11 Complete first draft of all subsystem descriptions wrt !170.
    Former-commit-id: c2a877f09ba3795a79e584d4f0658e7b96d010c0
2019-10-11 update tabulator Plando to reflect #198
    Former-commit-id: 5a9715961f4709d64888bf979ae26733256227c2
2019-10-16 revise section(s) on rebasing/merging for clarity around signing
    Former-commit-id: 2d35ca39d732f6c47e0ccc38cc77844c12dc8ef9
2019-10-18 Fully dimensioned PDF of paper attitude adjustment artifact. Replacing v1.
    Former-commit-id: 2ca7536488bb1238430d70320dbd2a9cf9e74c35
2019-10-18 Updated README and papers for on-boarding interested parties.
    Former-commit-id: eed3c16a4db6a4d2ad80574a69e8169d21a18d81
2019-10-23 Bump FreeRTOS
    Former-commit-id: 3f5a3cf6484a87ef786694d81939063ee14f28ba
2019-10-24 Rename SBB verification.md document
    Former-commit-id: ed602427e3000bcdcd168e2ebd654cd311caddf8
2019-10-24 Bump FreeRTOS
    Former-commit-id: 274e6ab68abe5aa30ed8be6f288de55b6db5e9b5
2019-10-25 Fix verification makefiles to include the right path for FreeRTOS headers
    Former-commit-id: 200a55cd948f387dde54c4d97b0dec1a3d2e0657
2019-10-28 Fix lingering malloc problems
    Former-commit-id: cd8a61a658f54491b77d033260aae6c39dd8fef8
2019-10-30 Remove verbose SD lib prints
    Former-commit-id: 0ce97e189c0f920bb22e9818e1b104c3db1e7eb0
2019-10-31 Initial commit
    Former-commit-id: 247f1722cb6c9c4daa87b891899edbe2584cb98f
2019-10-31 Lint on formatting
    Former-commit-id: 3bdbfe08416a48b3ea5f1fbdec9624a3a2969a8c
2019-10-31 Formatting fixes
    Former-commit-id: ad2bd31e06d5435bea91cdb379c2e53dd9892efa
2019-10-31 Small fixes
    Former-commit-id: 9a55faa54fb180dce3fcccd3b0160b68ce6225f2
2019-11-06 Move evidence server lando under lando dir.
    Former-commit-id: 19559795134d1323eab8a8d7ba3783df569c173a
2019-11-06 Apply suggestion to specs/lando/evidence_server/evidence_server.lando
    Former-commit-id: 2a7441b274bb90825dc4ed5a07cb873acea20899
2020-02-21 Updated version of cmake downloaded and added wget to get it.
    Former-commit-id: ba83b4a1de09e9fd57f40d703135bcbf7ef3e269
2020-02-21 move archival files to LFS
    Former-commit-id: de64b6594693663f7e291c3ebab65612d65bb43c
2020-02-21 reorganize developer docs
    Former-commit-id: 7d3c1c0cad8e0809be705cffa508c797d39f2441
2020-02-21 reorganize slides
    Former-commit-id: fe539845529ec4774fa219a10a99affa50441834
2020-02-21 clean up and relink bibliography readme
    Former-commit-id: c468fa7ad4a10742ec75d4357e930e3067335a71
2020-02-21 First version of broad-spectrum bootstrap docs.
    Former-commit-id: c786a228d456cc4aa539704151fd8faa4bd56531
2020-02-21 Update Registration_System.md
    Former-commit-id: 2d176887d821b64ab7725062a86712225f0bf6bd
2020-02-21 Full rewrite of description. MR !173 is ready for review.
    One requirement has an open question in the MR discussion.
    Former-commit-id: d42e86565d6f844fbc9c2ddacc0eda235a808356
2020-02-21 Added reference to RFC 2119.
    Former-commit-id: 11ff6e8e5c18c1115794aabe6e41b6b326b5b321
2020-02-21 Add table summary of WP analysis for BVS-2019. Minor wording corrections.
    Former-commit-id: 106a6b47f68583c22a575f036262f612936cf435
2020-02-21 Correction to markdown layout of table.
    Former-commit-id: 0a1fe93fcdbe3685f0f15e3d0fd701545b4ace49
2020-02-21 Minor updates for Catalina
    Former-commit-id: f5bca9b5a60294303c1b3c3e93192fda9f1e787b
2020-02-21 This is a Markdown document, not text.
    Former-commit-id: df38fa5bbb03208e6511f0d080995547ad9b5105
2020-02-28 WIP CS description, start enumerating requirements .
    Former-commit-id: 9aea3914e4df97d3c6fb36493b97ad49c7e8c042
2020-02-28 Rebase merge.
    Former-commit-id: 8ce98561dcfbf7f6221626ea745a2a3f683ceb18
2020-02-28 More comments.
    Former-commit-id: c287e768cdfdd04d8bd9618813c12a54fd7f375f
2020-02-29 add doWhile
    Former-commit-id: 65a7ab16fe9e9ec58aeb4e02f5b3c138f318c87f
2020-02-29 deparameterize Cryptol spec to allow processing in SAW
    Former-commit-id: 26137fa228374793f796f3b0b81d97a178b6647a
2020-02-29 Implement election reporting subsystem on the sbb side.
    Former-commit-id: 453ffec7204e3d4f8411a469ae6a606236271795
2020-02-29 Add ACSL specs.
    Former-commit-id: 59725979b878fd9e262edee704c57665839bfcd7
2020-03-01 Update to precise version of Z3 stipulated by Cryptol release.
    Former-commit-id: 5cf01ea3db3da646eb7de5424dab412cabe64e7e

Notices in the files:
parts and their libraries:
SparkFun-Connectors: Licensing: Creative Commons ShareAlike 4.0 International - https://creativecommons.org/licenses/by-sa/4.0
